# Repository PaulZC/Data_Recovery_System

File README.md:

# Data_Recovery_System

### ! Still Work In Progress - but more complete than it was !

This is the repository for the SuperBIT Data Recovery System (a.k.a. the data drop capsule).

The DRS comprises:
- Raspberry Pi equipped with: 1 x 512GB and 4 x 128GB (RAID1) SD data storage
- ATSAMD21G18 microcontroller as used on the Adafruit Feather M0 Adalogger and the Arduino Zero
- [u-blox MAX-M8Q GNSS receiver](https://www.u-blox.com/en/product/max-m8-series)
- Iridium 9603N Short Burst Data modem
- Maxtena M1600HCT-P-SMA antenna, shared via a Skyworks AS179-92LF RF switch
- two [servo-actuated](https://www.servoshop.co.uk/index.php?pid=HITHS82MG&area=Servo)
[Scott Archery release aids](https://scottarchery.com/collections/releases/products/shark-release): one for the tether and one for the parachute
- [Rocketman 4' parachute](https://the-rocketman.com/recovery-html/)
- Low extraction force power connector
- 3D-printed cover
- PU foam enclosure
- PVC launch tube

See [LEARN.md](./LEARN.md) for more details.

[PCB.md](./PCB.md) contains instructions on how to populate and test the PCB.

[PI.md](./PI.md) contains instructions on how to configure the Raspberry Pi.

[ASSEMBLY.md](./ASSEMBLY.md) contains instructions on how to prepare the DRS for flight.

[GoGoGo.md](./GoGoGo.md) contains instructions on how to release and track the DRS.

The schematic, PCB layout and Bill Of Materials can be found in [Data_Recovery_System_V1.pdf](./Data_Recovery_System_V1.pdf)

The BOM is also available in [Excel .xlsx format](./Data_Recovery_System_BOM.xlsx)

The [Eagle](./Eagle) directory contains the schematic and pcb design files.

The [Arduino](./Arduino) directory contains the Arduino code for the SAMD microcontroller.

The [Drawings](./Drawings) directory contains the drawings for the trigger linkage.

The [OpenSCAD](./OpenSCAD) directory contains the OpenSCAD and STL files for the 3D-printed cover, release crown/mount, and heatsink.

The Python software tools which need to be installed on the Raspberry Pi can be found the [DRS_Python_Tools repo](https://github.com/PaulZC/DRS_Python_Tools).

See [SERVO.md](./SERVO.md) for details on how to modify the HiTec servo for
high altitude operation.

See [SHARK.md](./SHARK.md) for details on how to modify the Scott Archery Shark release aid.

## Licence

This project is distributed under a Creative Commons Attribution + Share-alike (BY-SA) licence.
Please refer to section 5 of the licence for the "Disclaimer of Warranties and Limitation of Liability".

Enjoy!

**_Paul_**

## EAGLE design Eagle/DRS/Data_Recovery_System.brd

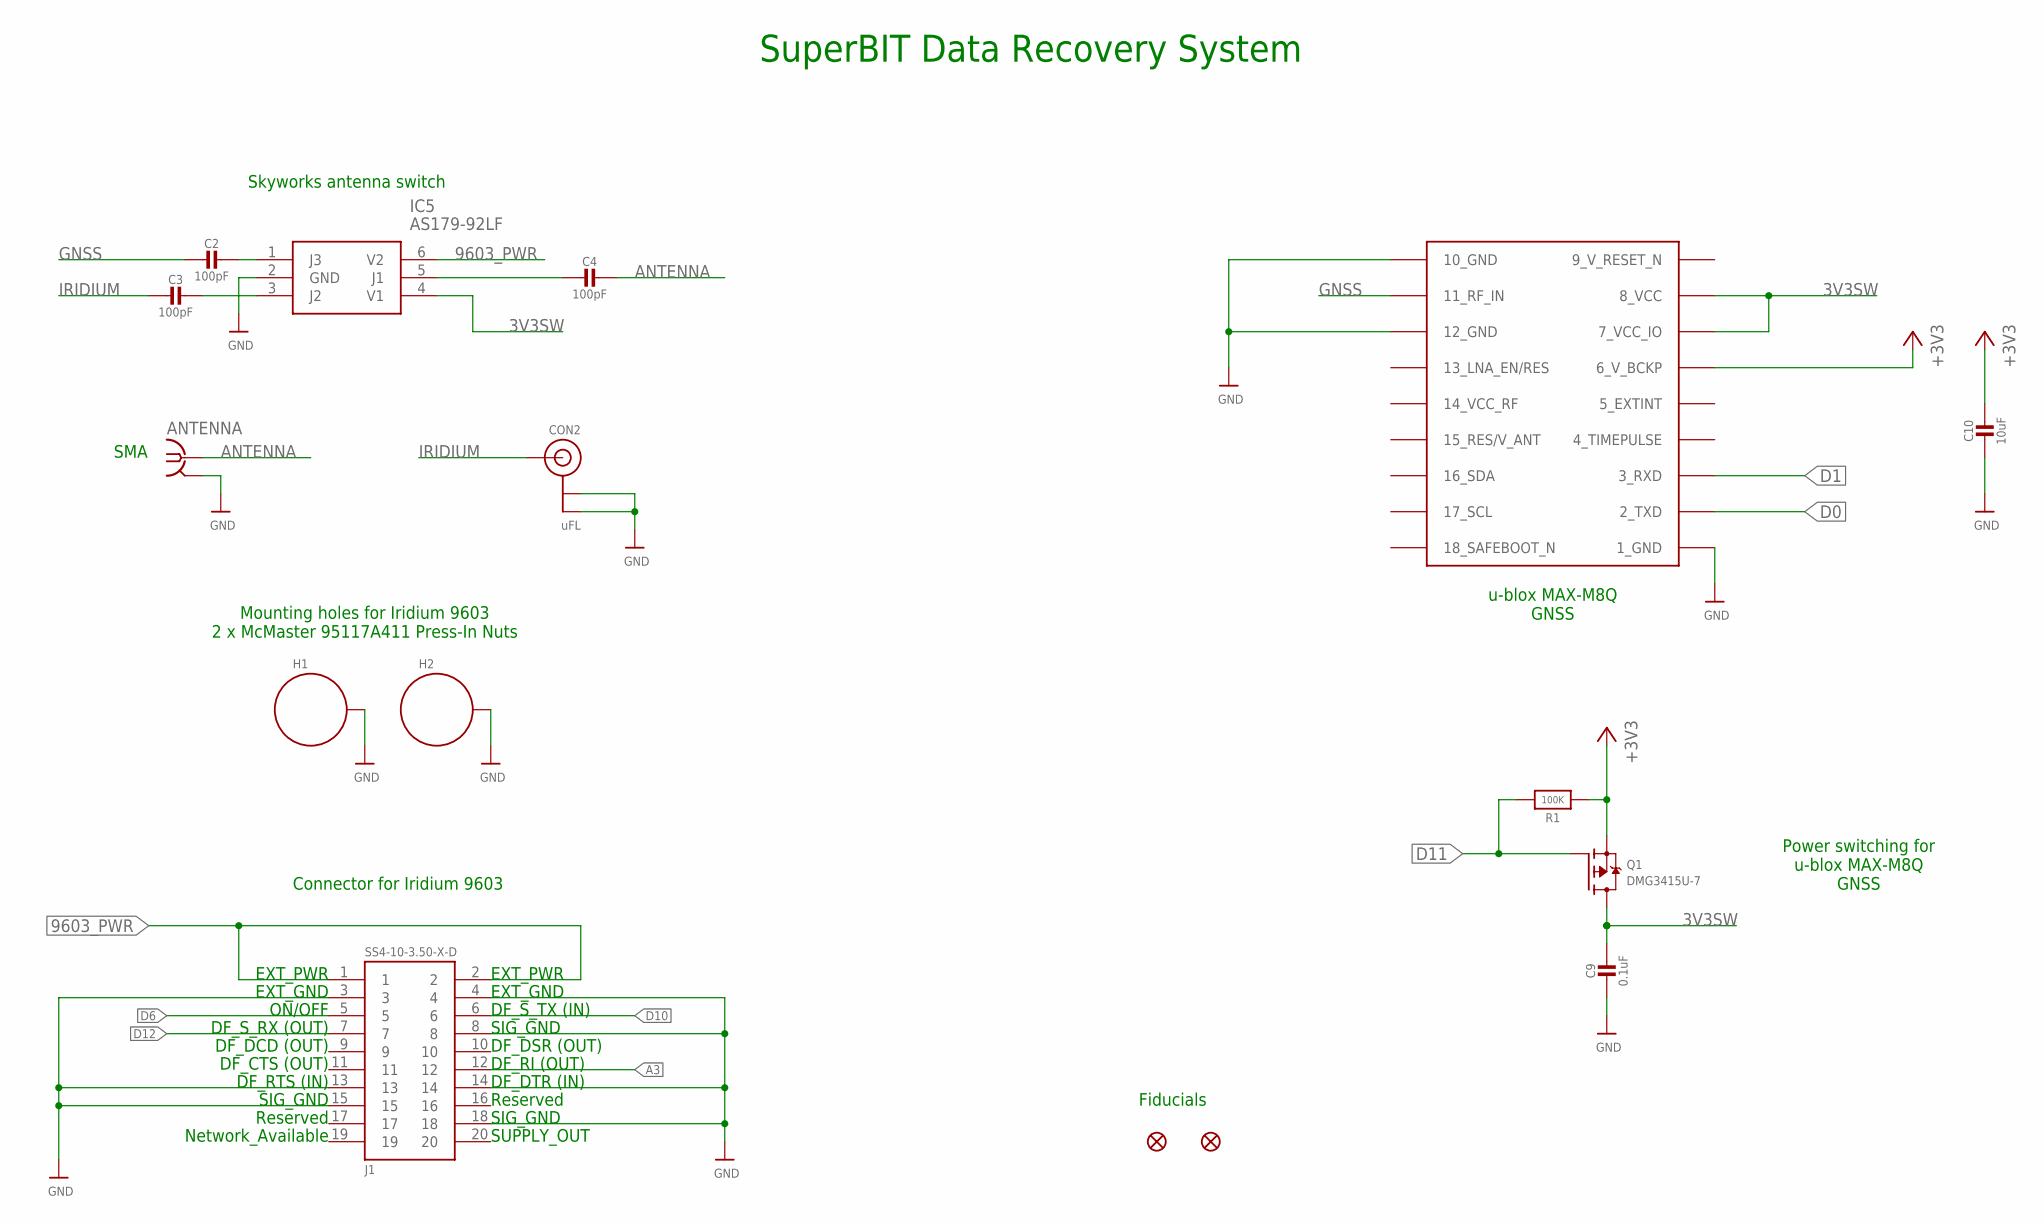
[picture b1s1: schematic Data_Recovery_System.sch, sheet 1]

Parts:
ANTENNA: SMA-142-0711-821/826; J502-ND-142-0711-821/826
C2, C3, C4: 100pF; 0603-NO@1
C9: 0.1uF; 0805-NO@1
C10: 10uF; 0805-NO@1
CON2: uFL; U.FL
FD1, FD2: FIDUCIAL1X2; FIDUCIAL-1X2
H1, H2: STANDOFF_ELECTRICALMCMASTER-95117A411; STANDOFF-ELECTRICAL-MCMASTER-95117A411
IC5: AS179-92LF; SOT65P220X100-6N
IC6: MAX-M8
J1: SS4-10-3.50-X-D
Q1: DMG3415U-7; SOT23-WIDE
R1: 100K; 0805-NO

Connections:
3V3SW: C9.1, IC5.4 (V1), IC6.7_VCC_IO, IC6.8_VCC, Q1.3 (D)
9_V_RESET_N: IC6.9_RESET_N (9_V_RESET_N)
9603_PWR: IC5.6 (V2), J1.1, J1.2; also elsewhere on the board
+3V3: C10.1, IC6.6_V_BCKP, Q1.2 (S), R1.1; also elsewhere on the board
A3: J1.12; also elsewhere on the board
ANTENNA: ANTENNA.1, C4.1
D0: IC6.2_TXD; also elsewhere on the board
D1: IC6.3_RXD; also elsewhere on the board
D6: J1.5; also elsewhere on the board
D10: J1.6; also elsewhere on the board
D11: Q1.1 (G), R1.2; also elsewhere on the board
D12: J1.7; also elsewhere on the board
GND: ANTENNA.G@1 (2), ANTENNA.G@2 (2), ANTENNA.G@3 (2), ANTENNA.G@4 (2), C9.2, C10.2, CON2.1 (GND), CON2.2 (GND), H1.P1, H2.P1, IC5.2 (GND), IC6.1_GND, IC6.10_GND, IC6.12_GND, J1.3, J1.4, J1.8, J1.13, J1.14, J1.15, J1.18; also elsewhere on the board
GNSS: C2.2, IC6.11_RF_IN
IRIDIUM: C3.2, CON2.3 (SIGNAL)
unnamed: C2.1, IC5.1 (J3)
unnamed: C3.1, IC5.3 (J2)
unnamed: C4.2, IC5.5 (J1)

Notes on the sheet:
Connector for Iridium 9603
Mounting holes for Iridium 9603 2 x McMaster 95117A411 Press-In Nuts
SuperBIT Data Recovery System
EXT_PWR
EXT_GND
ON/OFF
DF_S_RX (OUT)
DF_DCD (OUT)
DF_CTS (OUT)
DF_RTS (IN)
SIG_GND
Reserved
Network_Available
DF_S_TX (IN)
DF_DSR (OUT)
DF_RI (OUT)
DF_DTR (IN)
SUPPLY_OUT
Fiducials
u-blox MAX-M8Q GNSS
Power switching for u-blox MAX-M8Q GNSS
Skyworks antenna switch
SMA

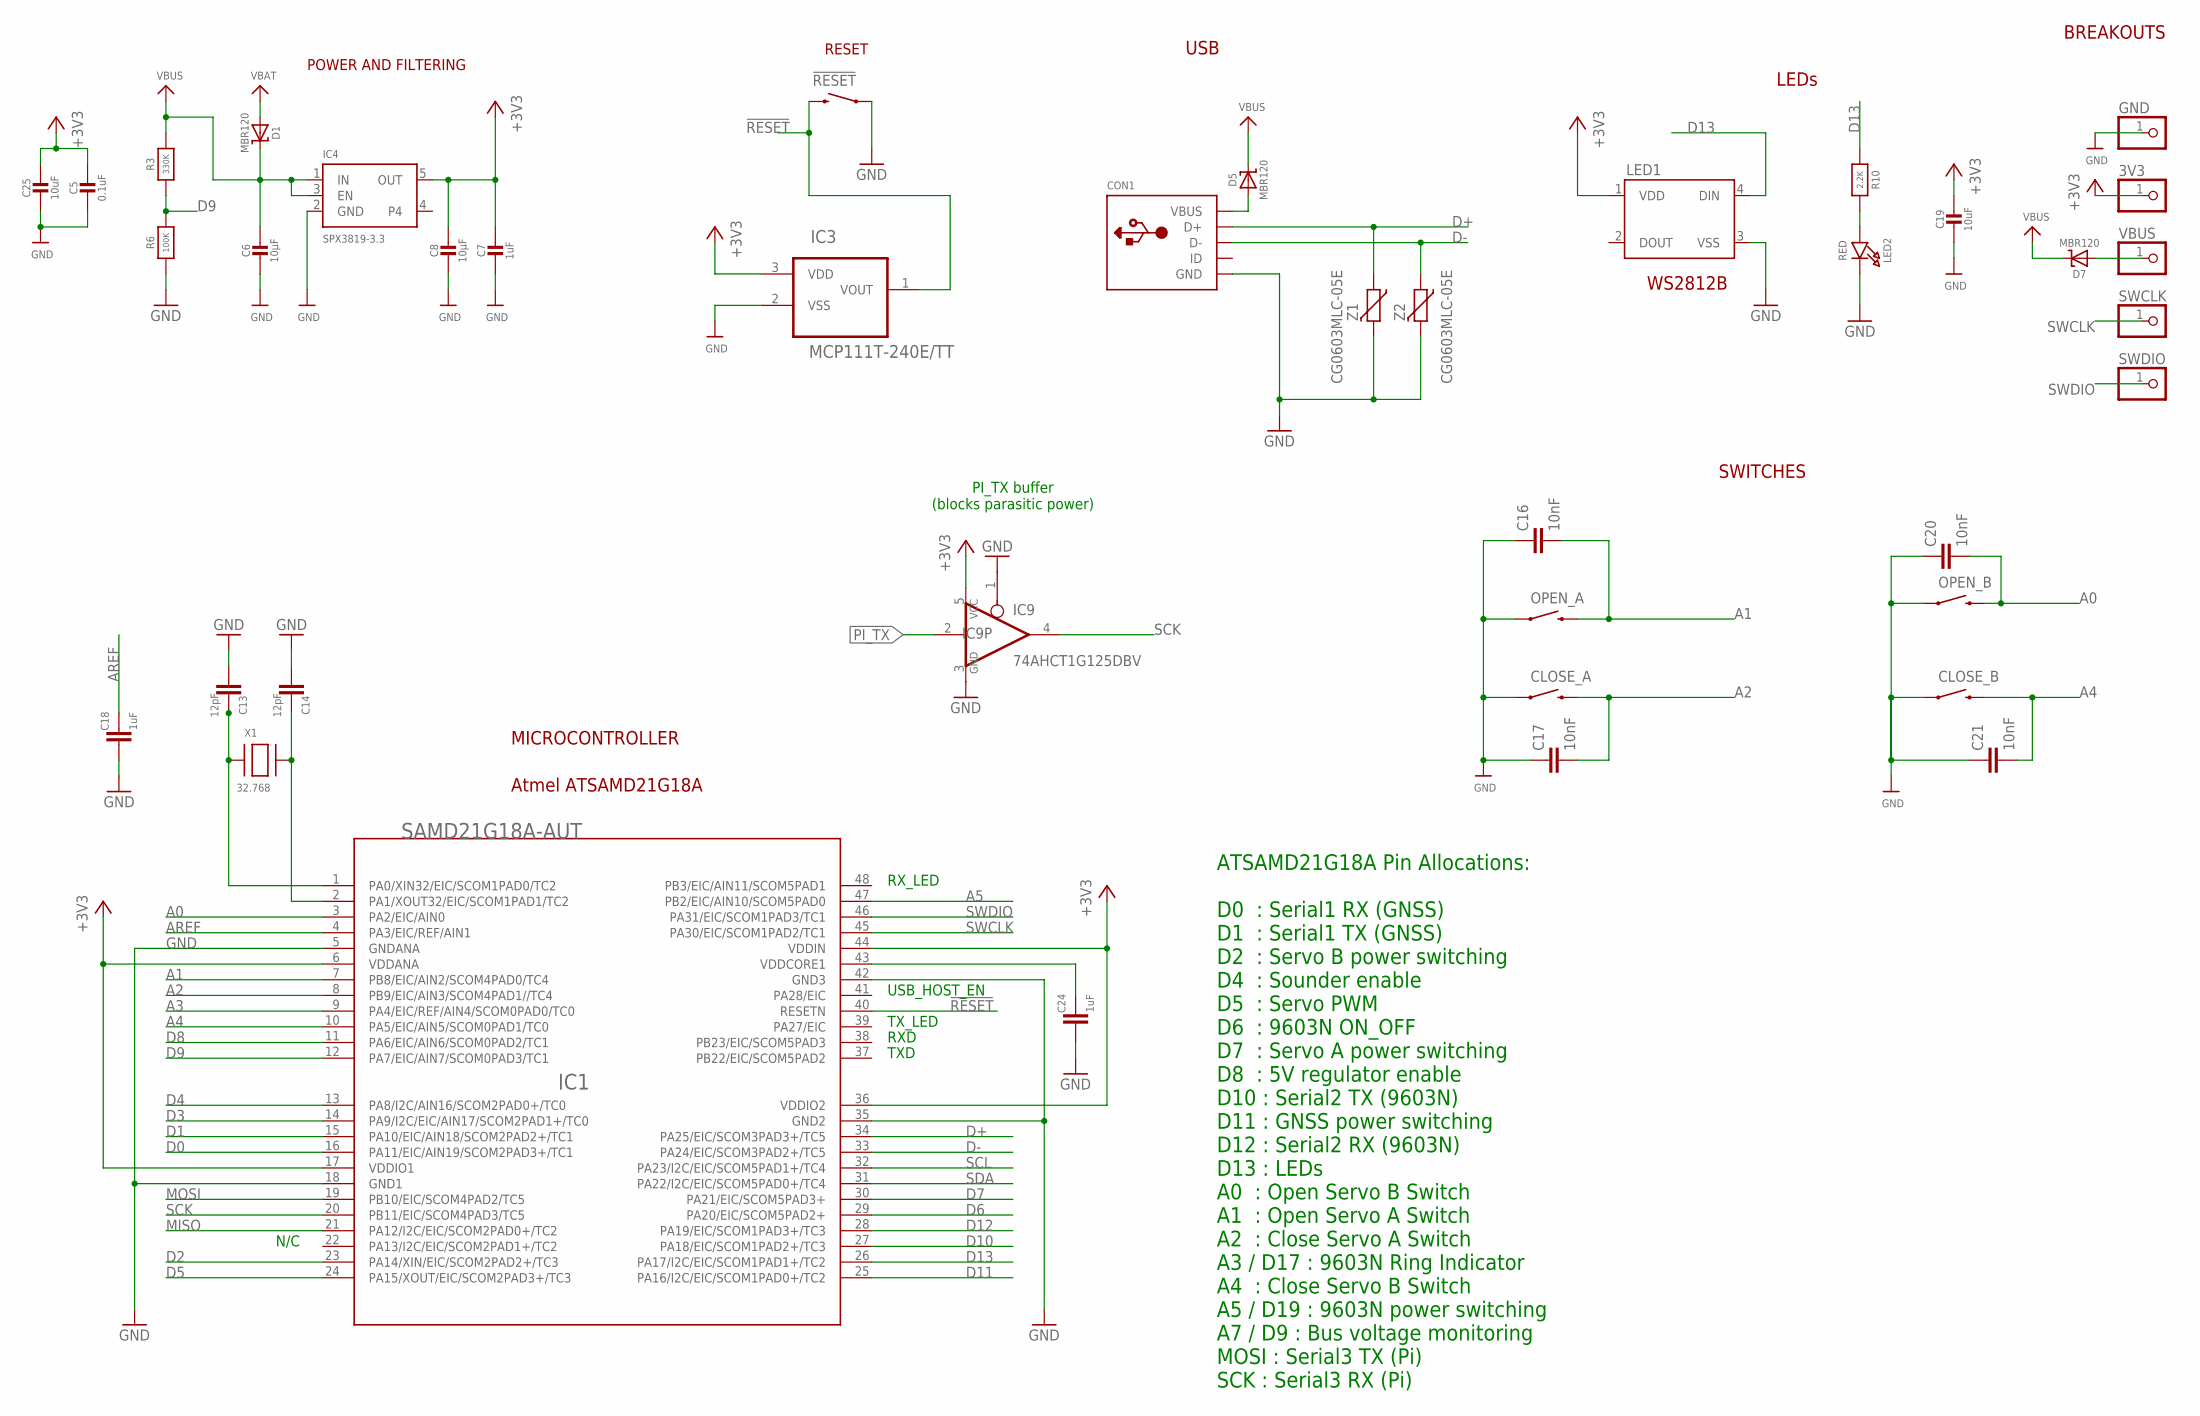
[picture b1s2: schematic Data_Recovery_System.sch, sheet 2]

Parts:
3V3: PINHD-1X1; 1X01
!RESET: SWITCH-MOMENTARY-2PTH; TACTILE-PTH
C5: 0.1uF; 0805-NO@1
C6, C8: 10µF; 0805-NO@1
C7: 1uF; 0603-NO@1
C13, C14: 12pF; C0603
C16, C17, C20, C21: 10nF; C0805
C18, C24: 1uF; C0603
C19, C25: 10uF; 0805-NO@1
CLOSE_A: SWITCH-MOMENTARY-2PTH; TACTILE-PTH
CLOSE_B: SWITCH-MOMENTARY-2PTH; TACTILE-PTH
CON1: MICROBUILDER_USBFCI_10103594_CORRECTED; MICROBUILDER_FCI_10103594_CORRECTED
D1, D5, D7: MBR120; SOD-123
GND: PINHD-1X1; 1X01
IC1: SAMD21G18A-AUT; TQFP48-7X7
IC3: MCP111T-240E/TT; SOT95P237X112-3N; MPN MCP111T-240E/TT
IC4: SPX3819-3.3; SOT23-5
IC9: 74AHCT1G125DBV; SOT23-5
LED1: WS2812B
LED2: RED; CHIPLED_0805_NOOUTLINE
OPEN_A: SWITCH-MOMENTARY-2PTH; TACTILE-PTH
OPEN_B: SWITCH-MOMENTARY-2PTH; TACTILE-PTH
R3: 330K; 0805-NO
R6: 100K; 0805-NO
R10: 2.2K; 0603-NO
SWCLK: PINHD-1X1; 1X01
SWDIO: PINHD-1X1; 1X01
VBUS: PINHD-1X1; 1X01
X1: 32.768; XTAL3215
Z1, Z2: CG0603MLC-05E; CT/CN0603

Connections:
!RESET: !RESET.3 (2), IC1.40 (RESETN), IC3.1 (VOUT)
+3V3: 3V3.1, C5.1, C7.1, C8.1, C19.1, C25.1, IC1.6 (VDDANA), IC1.17 (VDDIO1), IC1.36 (VDDIO2), IC1.44 (VDDIN), IC3.3 (VDD), IC4.5 (OUT), IC9.5 (VCC), LED1.1 (VDD); also elsewhere on the board
A0: C20.2, IC1.3 (PA2/EIC/AIN0), OPEN_B.3 (2)
A1: C16.2, IC1.7 (PB8/EIC/AIN2/SCOM4PAD0/TC4), OPEN_A.3 (2)
A2: C17.2, CLOSE_A.3 (2), IC1.8 (PB9/EIC/AIN3/SCOM4PAD1//TC4)
A3: IC1.9 (PA4/EIC/REF/AIN4/SCOM0PAD0/TC0); also elsewhere on the board
A4: C21.2, CLOSE_B.3 (2), IC1.10 (PA5/EIC/AIN5/SCOM0PAD1/TC0)
A5: IC1.47 (PB2/EIC/AIN10/SCOM5PAD0); also elsewhere on the board
AREF: C18.1, IC1.4 (PA3/EIC/REF/AIN1)
D0: IC1.16 (PA11/EIC/AIN19/SCOM2PAD3+/TC1); also elsewhere on the board
D1: IC1.15 (PA10/EIC/AIN18/SCOM2PAD2+/TC1); also elsewhere on the board
D2: IC1.23 (PA14/XIN/EIC/SCOM2PAD2+/TC3); also elsewhere on the board
D3: IC1.14 (PA9/I2C/EIC/AIN17/SCOM2PAD1+/TC0)
D4: IC1.13 (PA8/I2C/AIN16/SCOM2PAD0+/TC0); also elsewhere on the board
D5: IC1.24 (PA15/XOUT/EIC/SCOM2PAD3+/TC3); also elsewhere on the board
D6: IC1.29 (PA20/EIC/SCOM5PAD2+); also elsewhere on the board
D7: IC1.30 (PA21/EIC/SCOM5PAD3+); also elsewhere on the board
D8: IC1.11 (PA6/EIC/AIN6/SCOM0PAD2/TC1); also elsewhere on the board
D9: IC1.12 (PA7/EIC/AIN7/SCOM0PAD3/TC1), R3.1, R6.2
D10: IC1.27 (PA18/EIC/SCOM1PAD2+/TC3); also elsewhere on the board
D11: IC1.25 (PA16/I2C/EIC/SCOM1PAD0+/TC2); also elsewhere on the board
D12: IC1.28 (PA19/EIC/SCOM1PAD3+/TC3); also elsewhere on the board
D13: IC1.26 (PA17/I2C/EIC/SCOM1PAD1+/TC2), LED1.4 (DIN), R10.1
D+: CON1.D+, IC1.34 (PA25/EIC/SCOM3PAD3+/TC5), Z1.1
D-: CON1.D-, IC1.33 (PA24/EIC/SCOM3PAD2+/TC5), Z2.1
GND: !RESET.1, C5.2, C6.2, C7.2, C8.2, C13.2, C14.2, C16.1, C17.1, C18.2, C19.2, C20.1, C21.1, C24.2, C25.2, CLOSE_A.1, CLOSE_B.1, CON1.BASE@1 (GND), CON1.BASE@2 (GND), CON1.GND, CON1.SPRT@1 (GND), CON1.SPRT@2 (GND), CON1.SPRT@3 (GND), CON1.SPRT@4 (GND), GND.1, IC1.5 (GNDANA), IC1.18 (GND1), IC1.35 (GND2), IC1.42 (GND3), IC3.2 (VSS), IC4.2 (GND), IC9.1 (OE), IC9.3 (GND), LED1.3 (VSS), LED2.C, OPEN_A.1, OPEN_B.1, R6.1, Z1.2, Z2.2; also elsewhere on the board
MISO: IC1.21 (PA12/I2C/EIC/SCOM2PAD0+/TC2)
MOSI: IC1.19 (PB10/EIC/SCOM4PAD2/TC5); also elsewhere on the board
unnamed: C13.1, IC1.1 (PA0/XIN32/EIC/SCOM1PAD0/TC2), X1.P$1
unnamed: C14.1, IC1.2 (PA1/XOUT32/EIC/SCOM1PAD1/TC2), X1.P$2
unnamed: LED2.A, R10.2
unnamed: CON1.VBUS, D5.A
unnamed: D7.A, VBUS.1
PI_TX: IC9.2 (I); also elsewhere on the board
SCK: IC1.20 (PB11/EIC/SCOM4PAD3/TC5), IC9.4 (O)
SCL: IC1.32 (PA23/I2C/EIC/SCOM5PAD1+/TC4)
SDA: IC1.31 (PA22/I2C/EIC/SCOM5PAD0+/TC4)
SWCLK: IC1.45 (PA30/EIC/SCOM1PAD2/TC1), SWCLK.1
SWDIO: IC1.46 (PA31/EIC/SCOM1PAD3/TC1), SWDIO.1
VBAT: D1.A; also elsewhere on the board
VBUS: C6.1, D1.C, D5.C, D7.C, IC4.1 (IN), IC4.3 (EN), R3.2
VDDCORE2: C24.1, IC1.43 (VDDCORE1)

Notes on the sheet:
MICROCONTROLLER
USB_HOST_EN
TXD
RXD
TX_LED
RX_LED
Atmel ATSAMD21G18A
N/C
POWER AND FILTERING
RESET
USB
BREAKOUTS
LEDs
WS2812B
SWITCHES
ATSAMD21G18A Pin Allocations: D0 : Serial1 RX (GNSS) D1 : Serial1 TX (GNSS) D2 : Servo B power switching D4 : Sounder enable D5 : Servo PWM D6 : 9603N ON_OFF D7 : Servo A power switching D8 : 5V regulator enable D10 : Serial2 TX (9603N) D11 : GNSS power switching D12 : Serial2 RX (9603N) D13 : LEDs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
PI_TX buffer (blocks parasitic power)

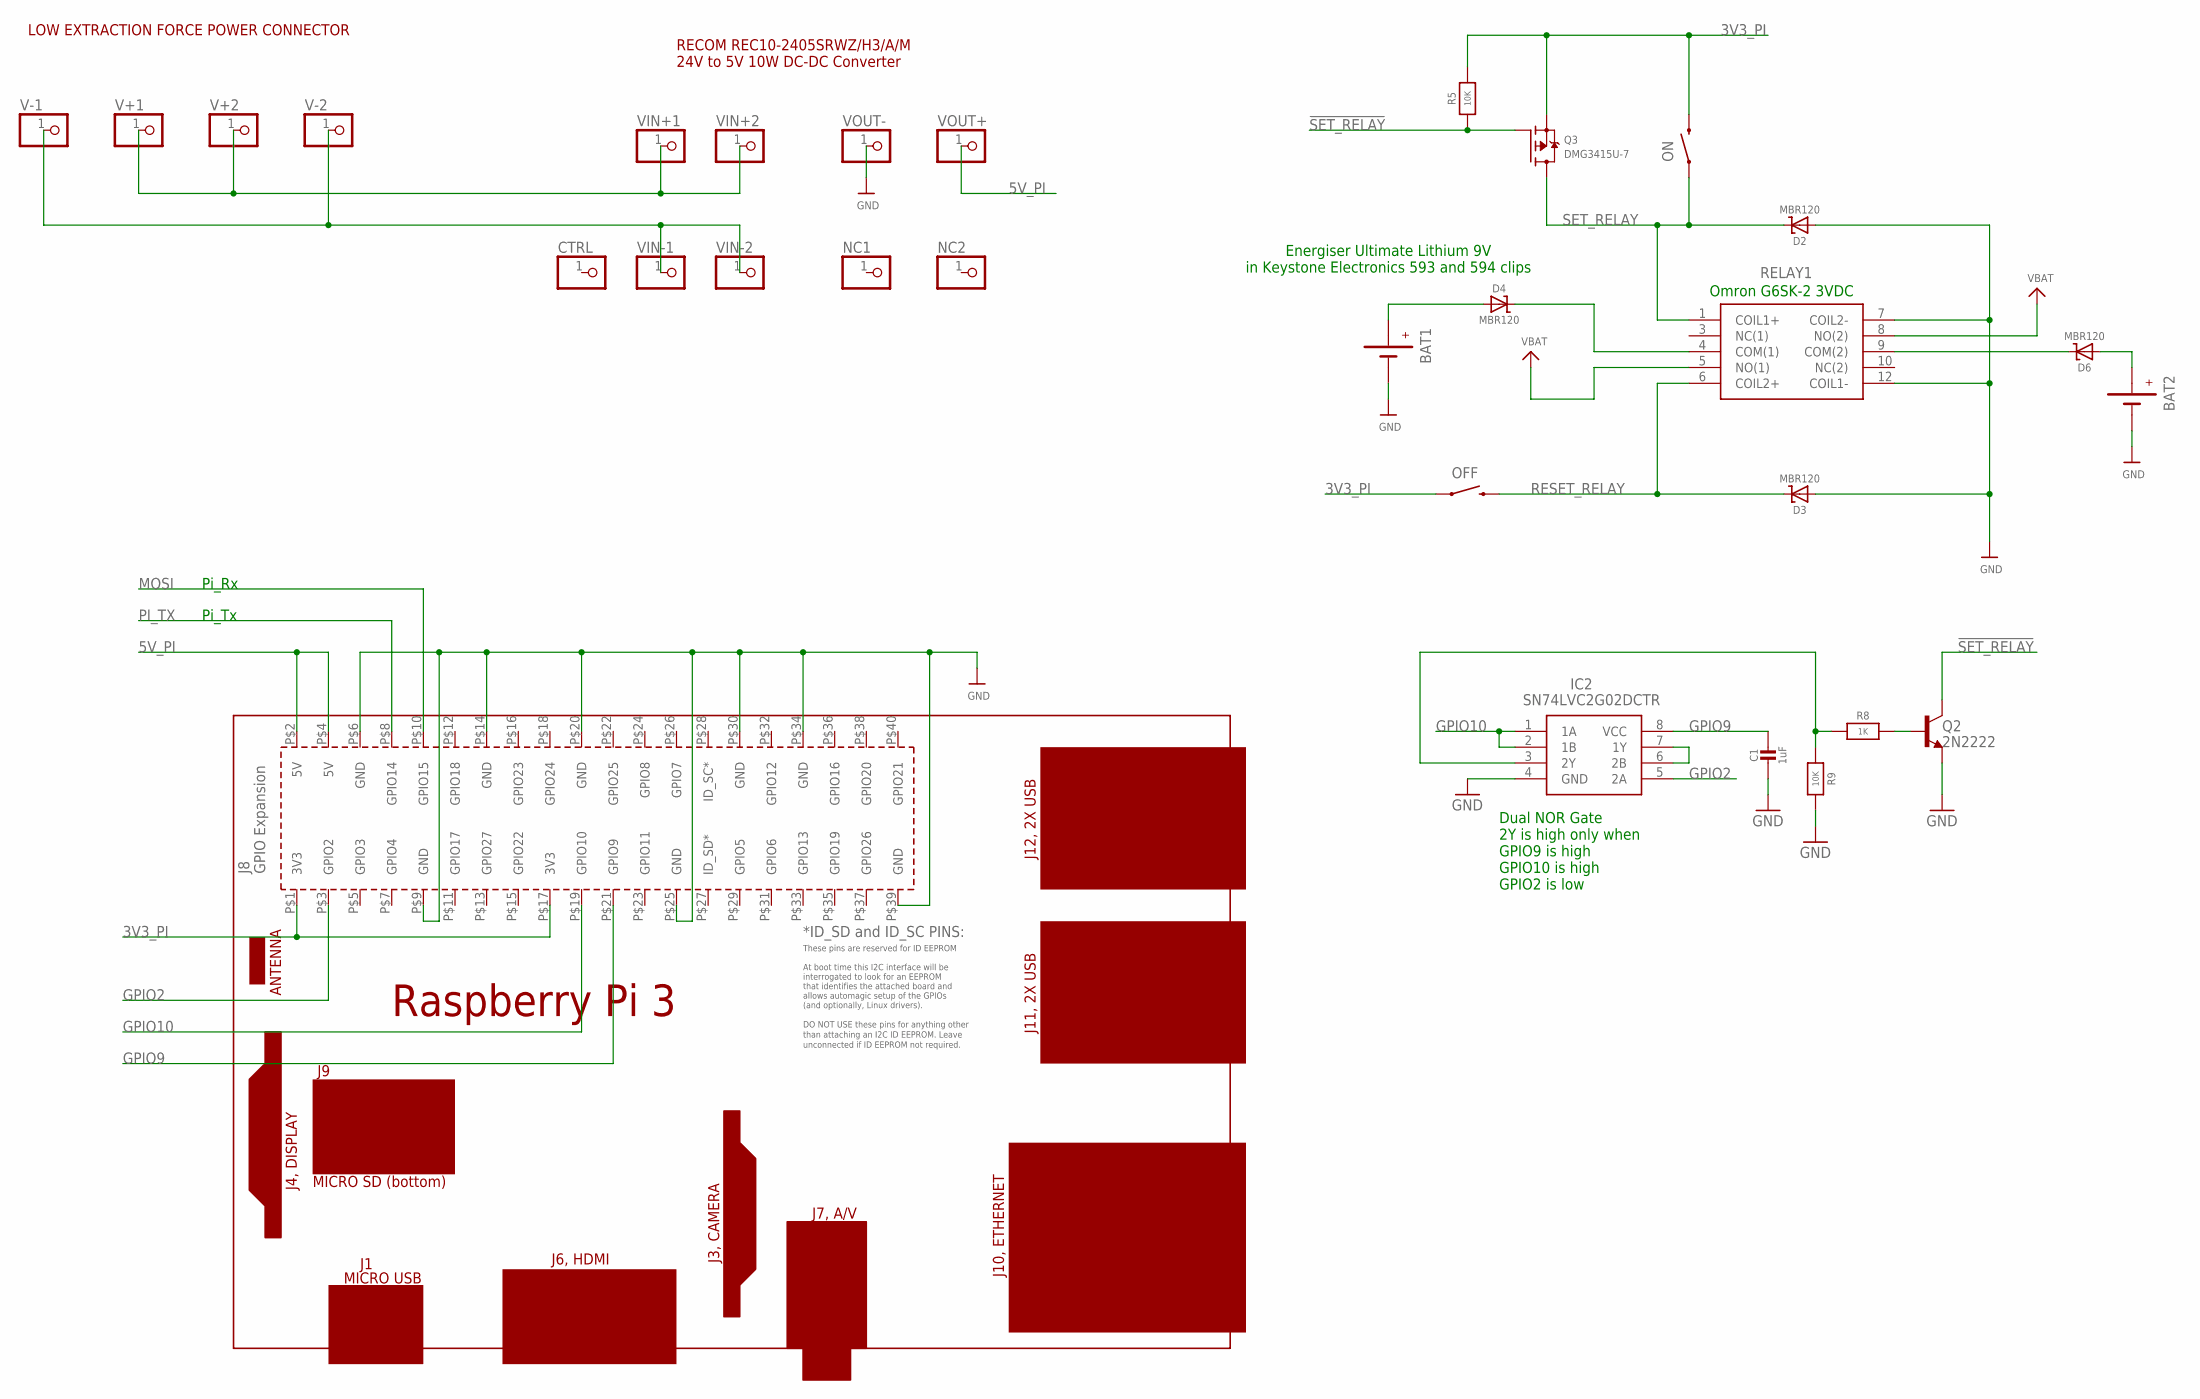
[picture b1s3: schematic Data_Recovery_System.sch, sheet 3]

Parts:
BAT1, BAT2: BATTERYBATTERY-9V-KEYSTONE-593-594; BATTERY-9V-KEYSTONE-593-594
C1: 1uF; 0603-NO@1
CTRL: PINHD-1X1; 1X01
D2, D3, D4, D6: MBR120; SOD-123
IC2: SN74LVC2G02DCTR; SOP65P400X130-8N
NC1, NC2: PINHD-1X1; 1X01
OFF: SWITCH-MOMENTARY-2PTH; TACTILE-PTH
ON: SWITCH-MOMENTARY-2PTH; TACTILE-PTH
PCB1: RPI3
Q2: 2N2222; SOT23-BEC
Q3: DMG3415U-7; SOT23-WIDE
R5: 10K; 0805-NO
R8: 1K; 0603-NO
R9: 10K; 0603-NO
RELAY1: G6SK-2_DC5; G6SK2DC5
V+1, V+2: PINHD-1X1; 1X01
V-1, V-2: PINHD-1X1; 1X01
VIN+1, VIN+2: PINHD-1X1; 1X01
VIN-1, VIN-2: PINHD-1X1; 1X01
VOUT+: PINHD-1X1; 1X01
VOUT-: PINHD-1X1; 1X01

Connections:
3V3_PI: OFF.1, ON.3 (2), PCB1.P$1 (3V3), PCB1.P$17 (3V3), Q3.2 (S), R5.2
5V_PI: PCB1.P$2 (5V), PCB1.P$4 (5V), VOUT+.1
!SET_RELAY: Q2.C, Q3.1 (G), R5.1
GND: BAT1.GND (-), BAT1.GND1 (-), BAT1.GND2 (-), BAT2.GND (-), BAT2.GND1 (-), BAT2.GND2 (-), C1.2, D2.A, D3.A, IC2.4 (GND), PCB1.P$6 (GND), PCB1.P$9 (GND), PCB1.P$14 (GND), PCB1.P$20 (GND), PCB1.P$25 (GND), PCB1.P$30 (GND), PCB1.P$34 (GND), PCB1.P$39 (GND), Q2.E, R9.2, RELAY1.7 (COIL2-), RELAY1.12 (COIL1-), VOUT-.1; also elsewhere on the board
GPIO2: IC2.5 (2A), PCB1.P$3 (GPIO2)
GPIO9: C1.1, IC2.8 (VCC), PCB1.P$21 (GPIO9)
GPIO10: IC2.1 (1A), IC2.2 (1B), PCB1.P$19 (GPIO10)
MOSI: PCB1.P$10 (GPIO15); also elsewhere on the board
unnamed: V-1.1, V-2.1, VIN-1.1, VIN-2.1
unnamed: D6.C, RELAY1.9 (COM(2))
unnamed: BAT2.PWR (+), BAT2.PWR1 (+), BAT2.PWR2 (+), D6.A
unnamed: BAT1.PWR (+), BAT1.PWR1 (+), BAT1.PWR2 (+), D4.A
unnamed: D4.C, RELAY1.4 (COM(1))
unnamed: Q2.B, R8.2
unnamed: IC2.3 (2Y), R8.1, R9.1
unnamed: IC2.6 (2B), IC2.7 (1Y)
PI_TX: PCB1.P$8 (GPIO14); also elsewhere on the board
RESET_RELAY: D3.C, OFF.3 (2), RELAY1.6 (COIL2+)
SET_RELAY: D2.C, ON.1, Q3.3 (D), RELAY1.1 (COIL1+)
VBAT: RELAY1.5 (NO(1)), RELAY1.8 (NO(2)); also elsewhere on the board
V_EXT: V+1.1, V+2.1, VIN+1.1, VIN+2.1

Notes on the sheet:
Omron G6SK-2 3VDC
Energiser Ultimate Lithium 9V in Keystone Electronics 593 and 594 clips
LOW EXTRACTION FORCE POWER CONNECTOR
RECOM REC10-2405SRWZ/H3/A/M 24V to 5V 10W DC-DC Converter
Dual NOR Gate 2Y is high only when GPIO9 is high GPIO10 is high GPIO2 is low
Pi_Tx
Pi_Rx

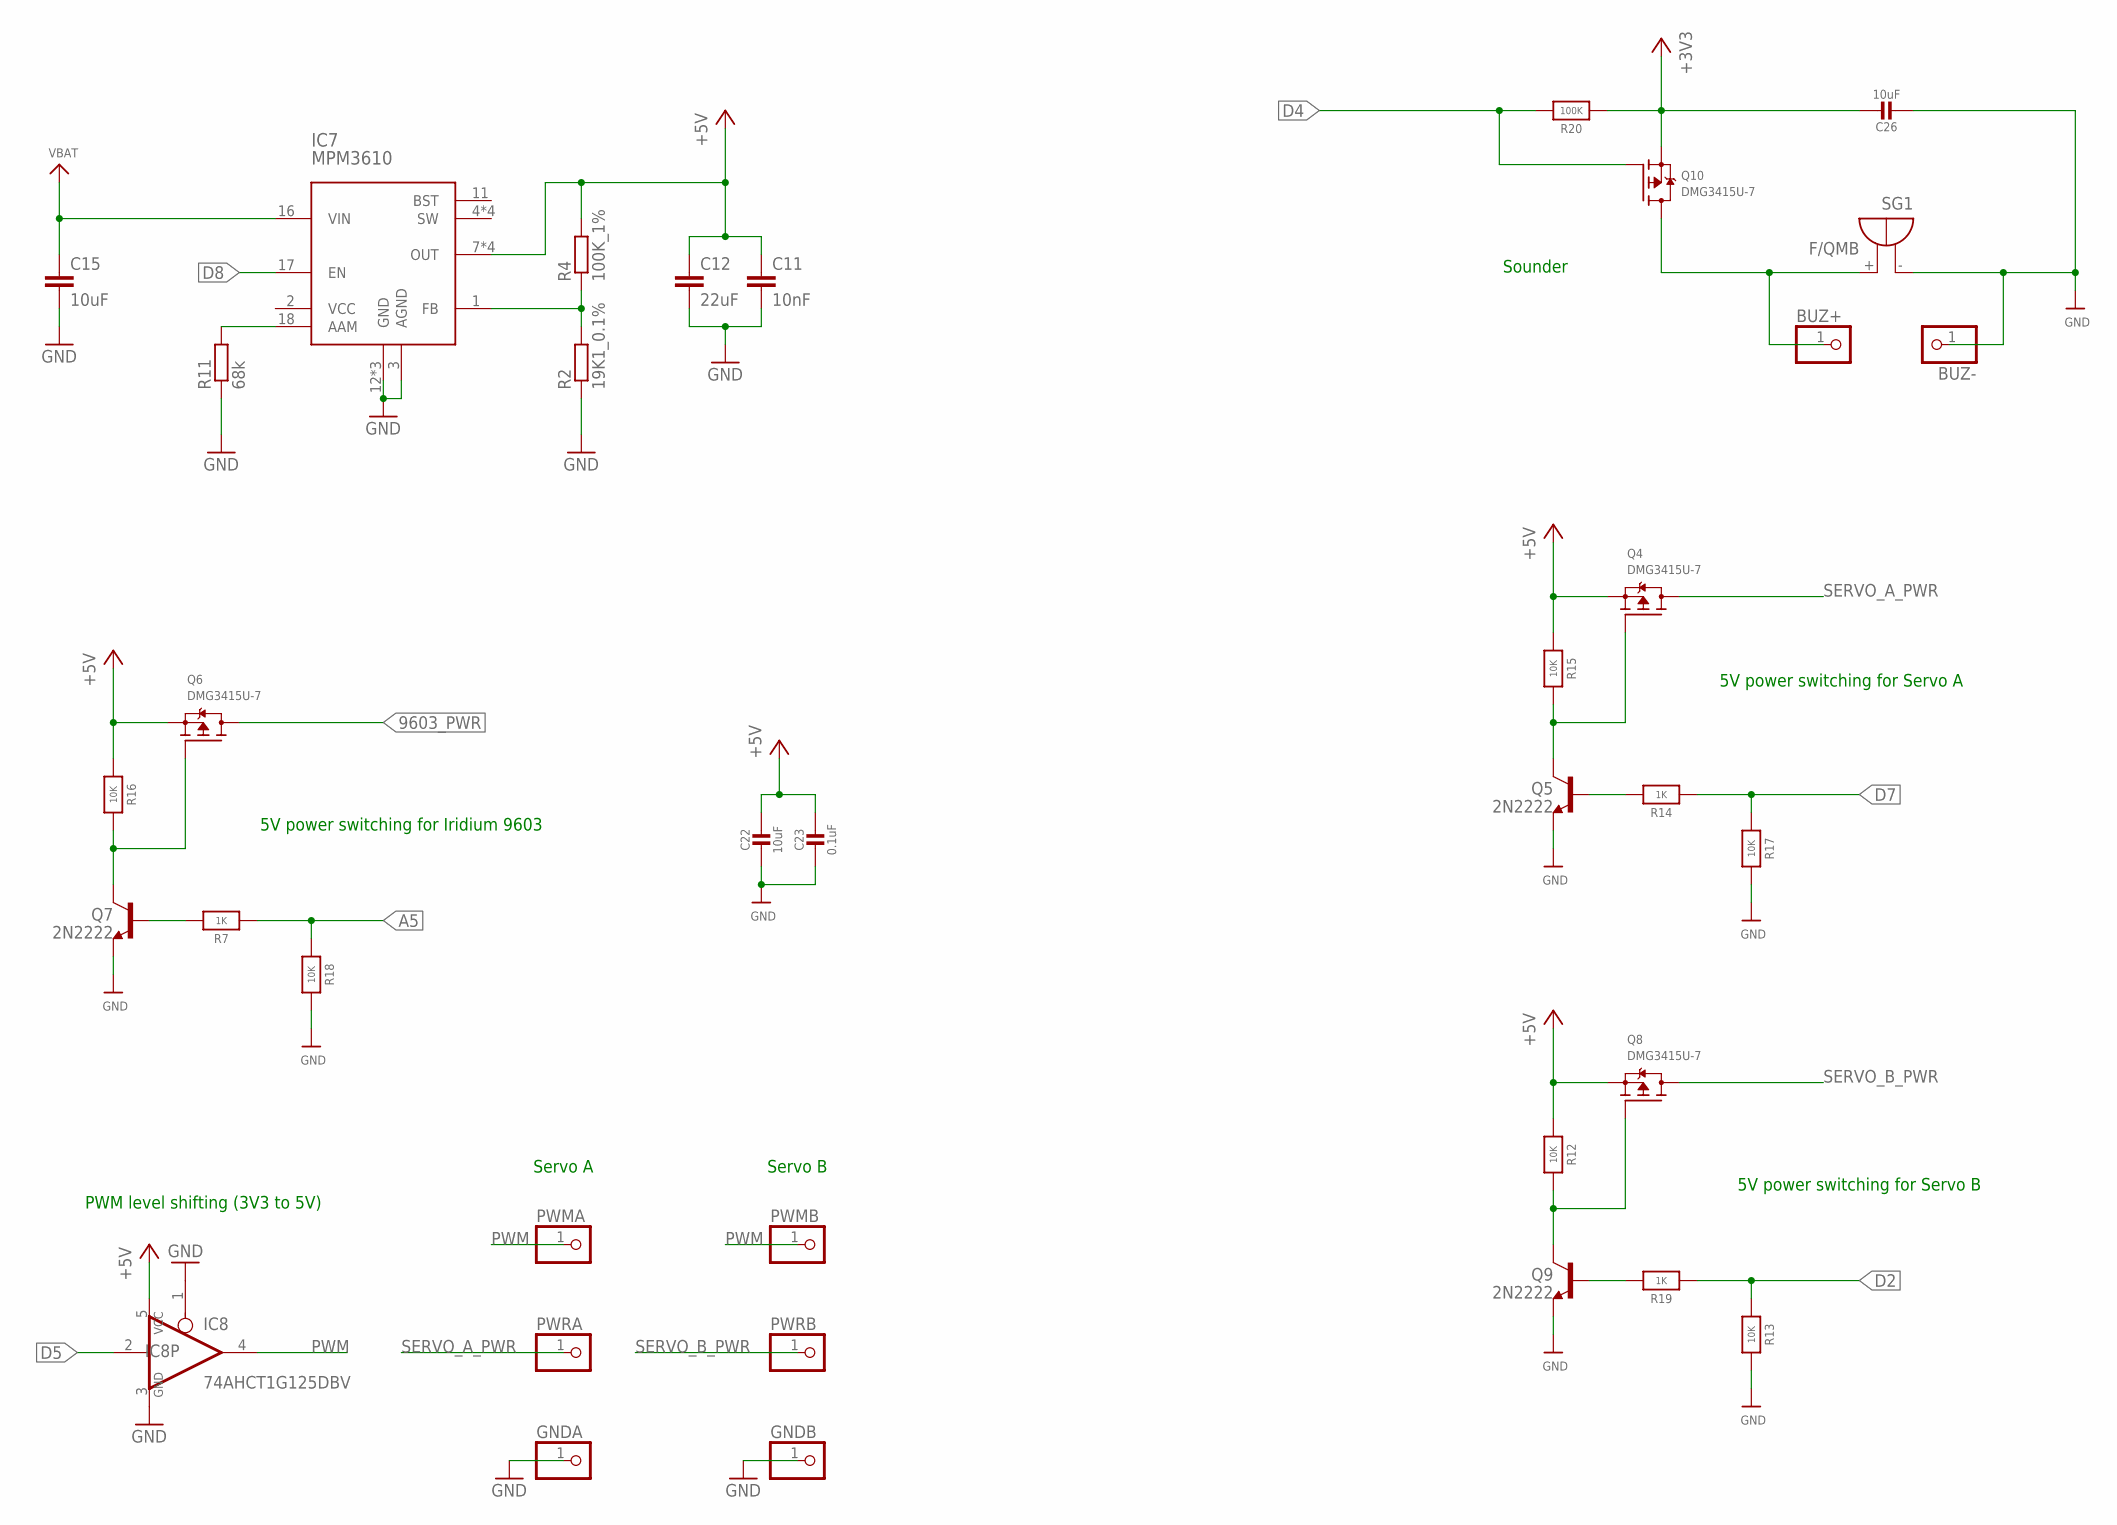
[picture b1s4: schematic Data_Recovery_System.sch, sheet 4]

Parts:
BUZ+: PINHD-1X1; 1X01
BUZ-: PINHD-1X1; 1X01
C11: 10nF; C0805
C12: 22uF; C0805
C15: 10uF; C0805
C22, C26: 10uF; 0805-NO@1
C23: 0.1uF; 0805-NO@1
GNDA: PINHD-1X1; 1X01
GNDB: PINHD-1X1; 1X01
IC7: MPM3610; QFN-20
IC8: 74AHCT1G125DBV; SOT23-5
PWMA: PINHD-1X1; 1X01
PWMB: PINHD-1X1; 1X01
PWRA: PINHD-1X1; 1X01
PWRB: PINHD-1X1; 1X01
Q4, Q6, Q8, Q10: DMG3415U-7; SOT23-WIDE
Q5, Q7, Q9: 2N2222; SOT23-BEC
R2: 19K1_0.1%; R0805
R4: 100K_1%; R0805
R7, R14, R19: 1K; 0603-NO
R11: 68k; R0805
R12, R13, R15, R16, R17, R18: 10K; 0603-NO
R20: 100K; 0805-NO
SG1: F/QMB

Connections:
9603_PWR: Q6.3 (D); also elsewhere on the board
+3V3: C26.1, Q10.2 (S), R20.1; also elsewhere on the board
+5V: C11.1, C12.1, C22.1, C23.1, IC7.7 (OUT), IC7.8 (OUT), IC7.9 (OUT), IC7.20 (OUT), IC8.5 (VCC), Q4.2 (S), Q6.2 (S), Q8.2 (S), R4.2, R12.1, R15.1, R16.1
A5: R7.1, R18.1; also elsewhere on the board
D2: R13.1, R19.1; also elsewhere on the board
D4: Q10.1 (G), R20.2; also elsewhere on the board
D5: IC8.2 (I); also elsewhere on the board
D7: R14.1, R17.1; also elsewhere on the board
D8: IC7.17 (EN); also elsewhere on the board
GND: BUZ-.1, C11.2, C12.2, C15.2, C22.2, C23.2, C26.2, GNDA.1, GNDB.1, IC7.3 (AGND), IC7.12 (GND), IC7.13 (GND), IC7.14 (GND), IC8.1 (OE), IC8.3 (GND), Q5.E, Q7.E, Q9.E, R2.1, R11.1, R13.2, R17.2, R18.2, SG1.- (+); also elsewhere on the board
unnamed: IC7.1 (FB), R2.2, R4.1
unnamed: Q7.B, R7.2
unnamed: Q6.1 (G), Q7.C, R16.2
unnamed: Q9.B, R19.2
unnamed: Q4.1 (G), Q5.C, R15.2
unnamed: Q5.B, R14.2
unnamed: Q8.1 (G), Q9.C, R12.2
unnamed: BUZ+.1, Q10.3 (D), SG1.+ (-)
unnamed: IC7.18 (AAM), R11.2
PWM: IC8.4 (O), PWMA.1, PWMB.1
SERVO_A_PWR: PWRA.1, Q4.3 (D)
SERVO_B_PWR: PWRB.1, Q8.3 (D)
VBAT: C15.1, IC7.16 (VIN); also elsewhere on the board

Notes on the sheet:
Servo A
Servo B
5V power switching for Servo A
5V power switching for Servo B
5V power switching for Iridium 9603
PWM level shifting (3V3 to 5V)
Sounder

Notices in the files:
Arduino/Data_Recovery_System_V1_Test/Data_Recovery_System_V1_Test.ino:
CC3 CC2 CC1 CC0 CC3 CC2 CC1 CC0
CC1 CC0 CC1 CC0
parts and their libraries:
microbuilder: This work is placed in the public domain, and may be freely used for commercial and non-commercial work with the following conditions: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
SparkFun-Electromechanical: Licensing: Creative Commons ShareAlike 4.0 International - https://creativecommons.org/licenses/by-sa/4.0
